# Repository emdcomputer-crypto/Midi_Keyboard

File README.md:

# 7-Key Custom MIDI Keypad

This is my 7-key MIDI keypad project for Hack Club Half Life Week 3 It features custom capacitive touch pads mx switches, a rotary encoder, slide potentiometers.
I used Kai Pereira's MIDI Keypad tutorial as a loose guide, but I customized the layout to make my own capacitive touch pads with a mix of rectangular and hexagonal shapes.

## What I Learned & How I Built It

1. **Making the Capacitive Touch Pads:** I designed the 7-key touch pads directly in KiCad's Footprint Editor. I made sure to uncheck `F.Paste` so solder paste won't be applied to the pads, leaving the copper exposed so it detects your finger. I also set a 0.5mm clearance gap between every key so they don't trigger each other.
2. **Routing the PCB:** I routed all the signal traces by hand, sticking to smooth 45-degree bends instead of sharp 90-degree corners to avoid acid traps or whatever that is.
3. **Fixing DRC Errors & Ground Pour:** I poured ground zones on both the top and bottom layers (`F.Cu` and `B.Cu`). I had a few "starved thermal" warnings where ground pads weren't getting enough copper spokes, so I ran short bridge traces from those pads to nearby ground areas. After that, DRC passed with 0 unconnected pads
4. **3D Models:** I set up the `HACKCLUB_3DMODEL_DIR` path variable in KiCad preferences so all the components show up properly in the 3D viewer.
5. **lack of gpio** due to the lack of gpio pins i had to sacrifice the leds for an extra button wich i wanted.

## Bill of Materials (BOM)

| Item | Category | Part Description | Qty | Price (USD) | Supplier | Link |
| :---: | :--- | :--- | :---: | :---: | :---: | :---: |
| **1** | Microcontroller | Waveshare ESP32-S3-Zero Dev Board | 1 | $9.88 | AliExpress | [Link](https://it.aliexpress.com/item/1005012733231291.html) |
| **2** | Keycaps | Relegendable Transparent Keycaps (10 Pcs) | 1 pack | $4.66 | AliExpress | [Link](https://it.aliexpress.com/item/1005005825113345.html) |
| **3** | Switches | Tactile Mechanical Switches (3-Pin MX) | 1 pack | $4.70 | AliExpress | [Link](https://it.aliexpress.com/item/1005013167413073.html) |
| **4** | Encoders | EC11 Rotary Encoders w/ Push Button (5 Pcs) | 1 pack | $3.53 | AliExpress | [Link](https://it.aliexpress.com/item/1005007644083514.html) |
| **5** | Potentiometers | 30mm Single Slide Potentiometer B5K (3 Pcs) | 1 pack | $1.94 | AliExpress | [Link](https://it.aliexpress.com/item/1005009637487801.html) |
| **6** | PCB | Custom PCB Fabrication | 5 pcs | $4.00 | JLCPCB | [Link](https://jlcpcb.com) |

(I chose the cheapest parts availble with free shipping from aliexpress but unfortunatley the price is this high to the tariffs we have in europe this also applies to jlc pcb where choosing the cheapest shipping may lead to it being more expensive becasue it doesnt include the tariffs and taxes so when in customs you can get asked to pay all of it, thats why i chose the cheapest shipping that also included all taxes paid )

### Cost 

* **Components Subtotal (AliExpress):** $24.71
* **AliExpress Shipping & Import Fees:** $25.40
* **JLCPCB (5 PCBs + Shipping):** $40.98
* **--------------------------------------------------**
* **Aprox Total Project Cost:** **$95.09 USD**
  
## Project Files

- `Hardware/Midi.kicad_sch` — KiCad schematic
- `Hardware/Midi.kicad_pcb` — KiCad PCB layout
- `Hardware/Midi.kicad_pro` — KiCad project file
- `FabricationFiles/` — Gerber zip and fabrication files for JLCPCB also includes a .step file 
- `Firmware/` — Firmware

## Credits

- Based on Kai Pereira's MIDI Keypad tutorial for Hack Club Half Life Week 3.
- Built using footprints and symbols from the Hack Club KiCad Library.

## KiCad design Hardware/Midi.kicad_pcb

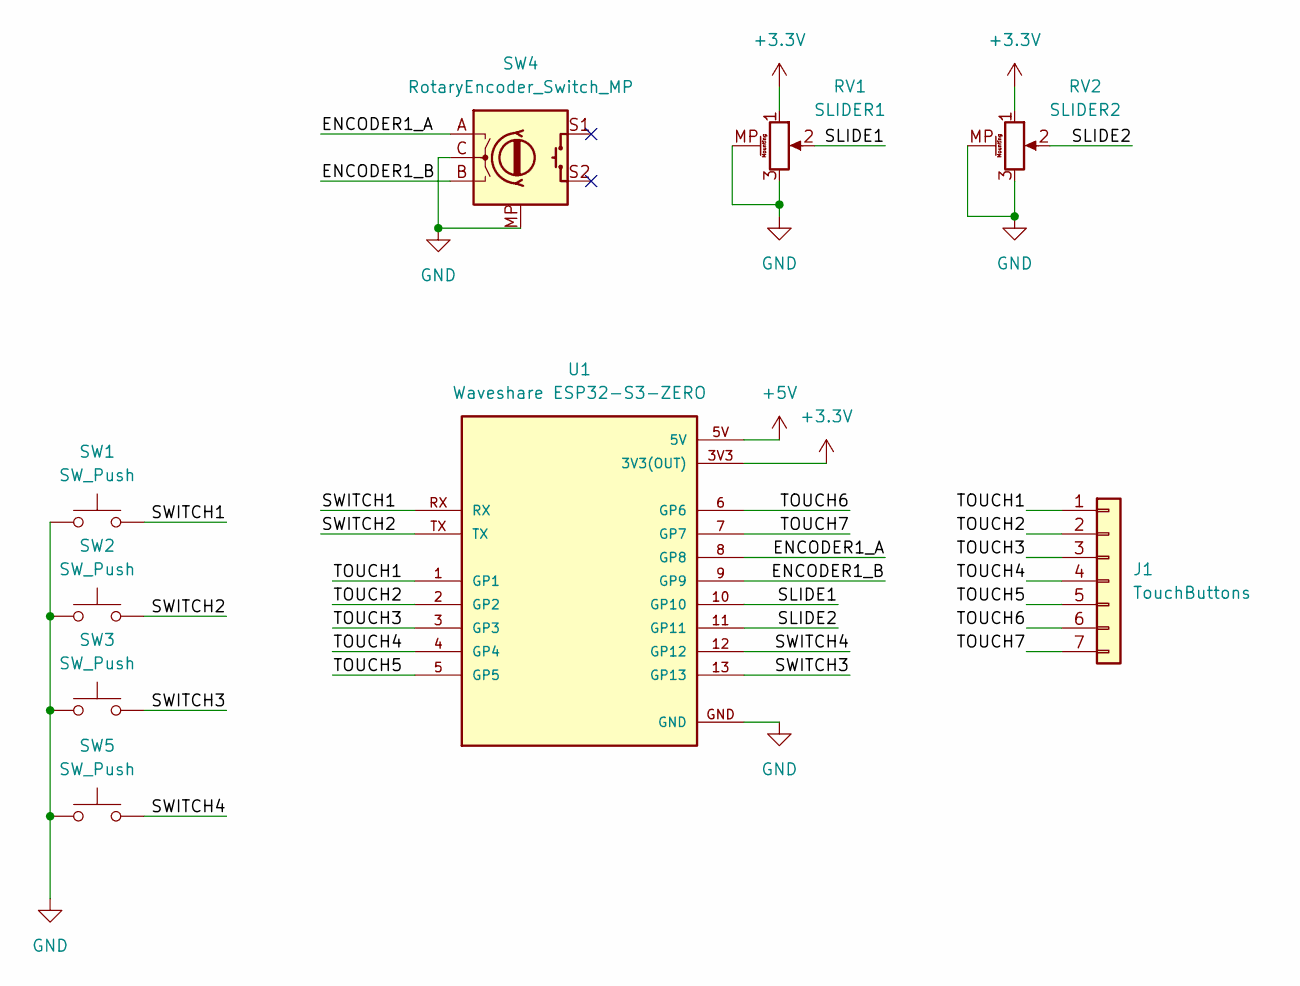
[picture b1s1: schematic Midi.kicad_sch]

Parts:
J1: TouchButtons; Keys
RV1: SLIDER1; Potentiometer_Bourns_PTA1543_Single_Slide
RV2: SLIDER2; Potentiometer_Bourns_PTA1543_Single_Slide
SW1, SW2, SW3, SW5: SW_Push; Kailh Choc Low-Profile Switches
SW4: RotaryEncoder_Switch_MP; RotaryEncoder_Alps_EC11E-Switch_Vertical_H20mm
U1: Waveshare ESP32-S3-ZERO; Waveshare ESP32-S3-Zero; PARTREV NA

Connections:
+3.3V: RV1.1, RV2.1, U1.3V3 (3V3(OUT))
+5V: U1.5V
/ENCODER1_A: SW4.A, U1.8 (GP8)
/ENCODER1_B: SW4.B, U1.9 (GP9)
/SLIDE1: RV1.2, U1.10 (GP10)
/SLIDE2: RV2.2, U1.11 (GP11)
/SWITCH1: SW1.2, U1.RX
/SWITCH2: SW2.2, U1.TX
/SWITCH3: SW3.2, U1.13 (GP13)
/SWITCH4: SW5.2, U1.12 (GP12)
/TOUCH1: J1.1, U1.1 (GP1)
/TOUCH2: J1.2, U1.2 (GP2)
/TOUCH3: J1.3, U1.3 (GP3)
/TOUCH4: J1.4, U1.4 (GP4)
/TOUCH5: J1.5, U1.5 (GP5)
/TOUCH6: J1.6, U1.6 (GP6)
/TOUCH7: J1.7, U1.7 (GP7)
GND: RV1.3, RV1.MP (MountPin), RV2.3, RV2.MP (MountPin), SW1.1, SW2.1, SW3.1, SW4.C, SW4.MP, SW5.1, U1.GND

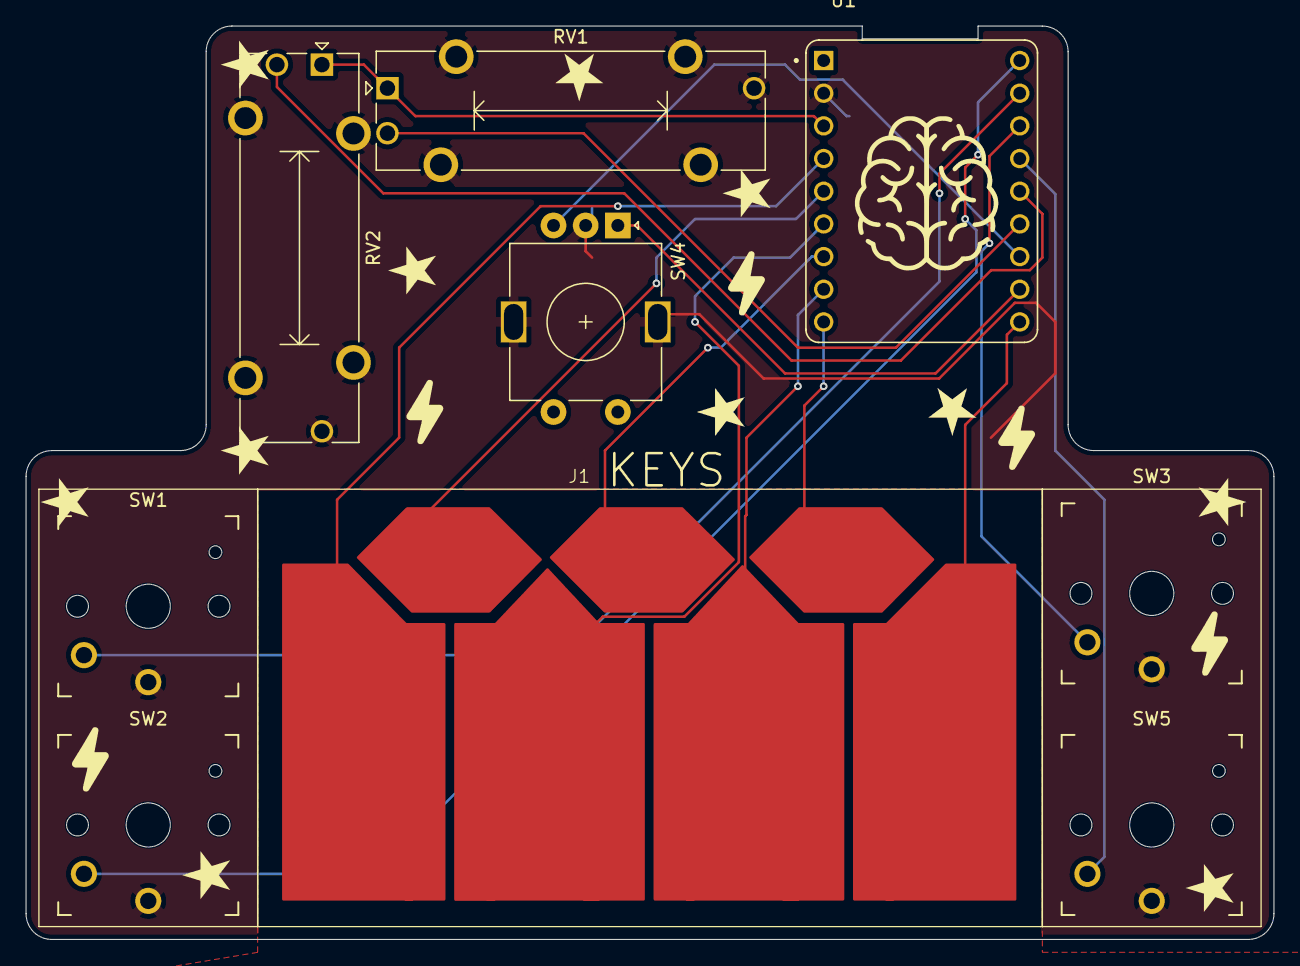
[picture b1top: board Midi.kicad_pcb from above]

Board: 2 copper layers, 97.0 x 71.0 mm, 9 parts (0 on the bottom side), 17 nets.
